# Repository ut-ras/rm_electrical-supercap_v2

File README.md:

# rm_electrical-supercap_v2

So i heard that having a readme is good and professional, so if anyone bothers to read this and is curious:
    The objective of the project is to use the excess allowed power draw. We chose the 90W at the time of writing I believe.
    Started out with a half bridge topology for the buck boose to/from 24V:3V supercaps.
    Apparently many compromises were made because Jed (Ged?) didn't want to use a microcontroller.
    So now we're at full bridge, using mspm0, with a lot of sensors and stuff so that zero voltage switching can be implemented to avoid power loss spike
    This specific branch, is a redesign to minimize powerpath (mainly), since we have more depth looking into the robot in our little compartment of space.

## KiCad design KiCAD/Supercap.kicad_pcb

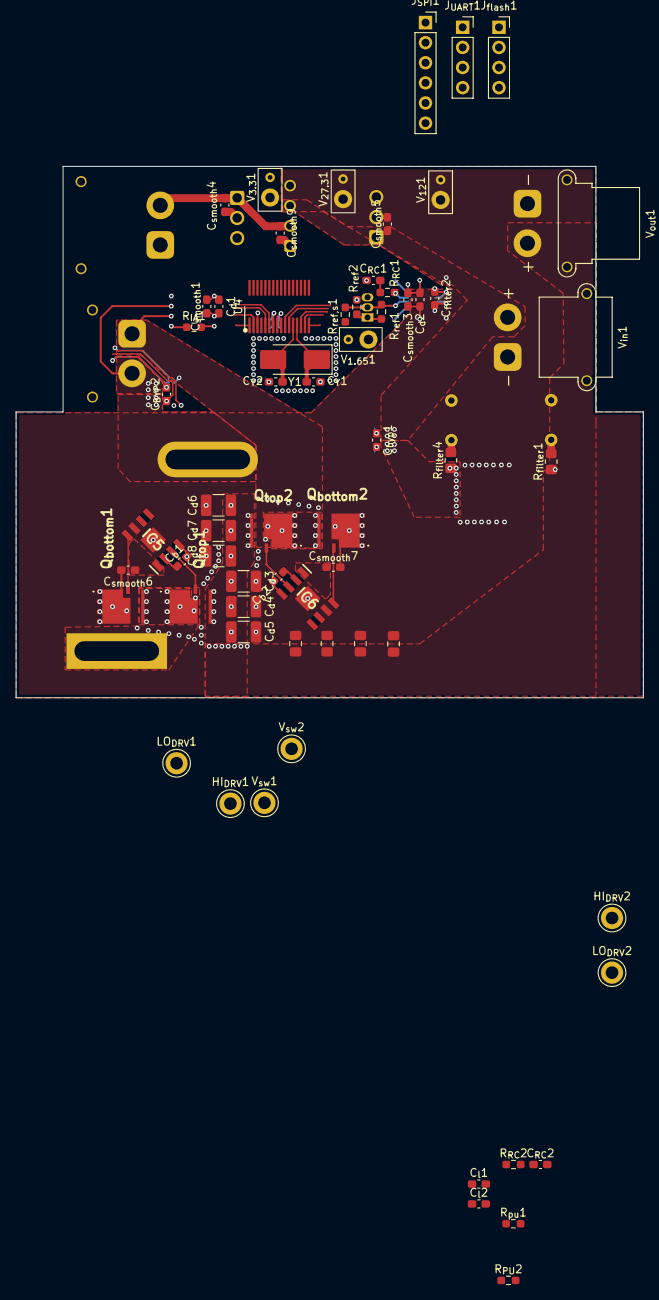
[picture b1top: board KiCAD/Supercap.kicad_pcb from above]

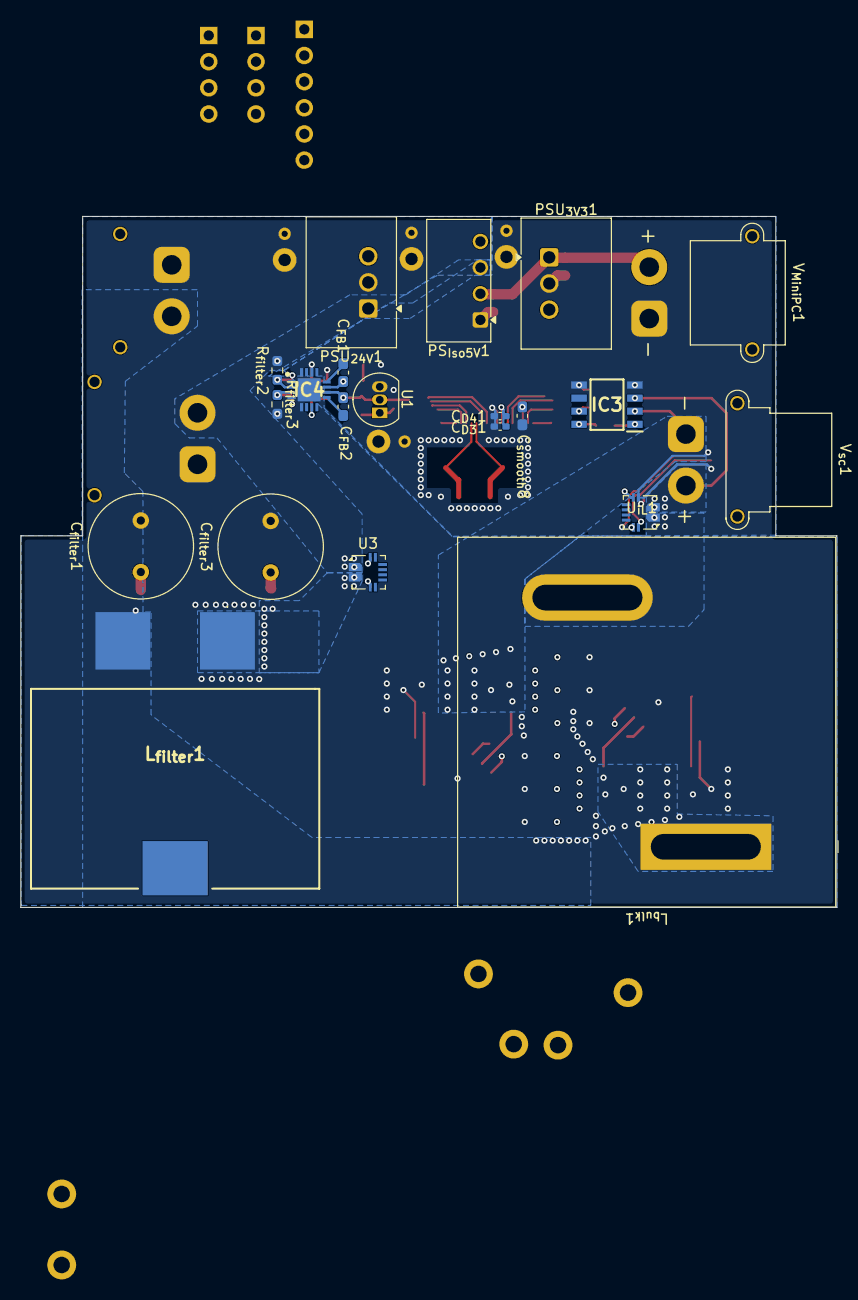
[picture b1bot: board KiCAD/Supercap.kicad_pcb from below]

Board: 4 copper layers, 79.2 x 67.1 mm, 84 parts (21 on the bottom side), 42 nets.

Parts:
C_{BYP}2: 0.1u; C_0603_1608Metric_Pad1.08x0.95mm_HandSolder
C_{D3}1: 100n; C_0402_1005Metric_Pad0.74x0.62mm_HandSolder
C_{D4}1: 10u; C_0402_1005Metric_Pad0.74x0.62mm_HandSolder
C_{FB}1, C_{FB}2: 100p; C_0603_1608Metric_Pad1.08x0.95mm_HandSolder
C_{RC}1, C_{RC}2: 1n; C_0603_1608Metric_Pad1.08x0.95mm_HandSolder
C_{Y}1, C_{Y}2: 10p; C_0603_1608Metric_Pad1.08x0.95mm_HandSolder
C_{bulk,out}1, C_{bulk,out}2, C_{bulk,out}3, C_{bulk,out}4: C_0805_2012Metric_Pad1.18x1.45mm_HandSolder
C_{byp}1: 0.1u; C_0603_1608Metric_Pad1.08x0.95mm_HandSolder
C_{b}1, C_{b}2: 1u; C_0603_1608Metric_Pad1.08x0.95mm_HandSolder
C_{d}1, C_{d}2: 0.1u; C_0603_1608Metric_Pad1.08x0.95mm_HandSolder
C_{d}3, C_{d}4, C_{d}5, C_{d}6, C_{d}7, C_{d}8: 10u; C_1210_3225Metric_Pad1.33x2.70mm_HandSolder
C_{filter}1, C_{filter}3: 1.2m; C_Radial_D10.0mm_H16.0mm_P5.00mm
C_{filter}2: 100p; C_0603_1608Metric_Pad1.08x0.95mm_HandSolder
C_{l}1, C_{l}2: 1n; C_0603_1608Metric_Pad1.08x0.95mm_HandSolder
C_{smooth}1, C_{smooth}3, C_{smooth}4, C_{smooth}5, C_{smooth}6, C_{smooth}7, C_{smooth}9: 4.7u; C_0603_1608Metric_Pad1.08x0.95mm_HandSolder
C_{smooth}8: 0.47u; C_0603_1608Metric_Pad1.08x0.95mm_HandSolder
HI_{DRV}1, HI_{DRV}2: TestPoint; TestPoint_Keystone_5010-5014_Multipurpose
IC3: INA823DT; SOIC127P600X175-8N
IC4: PGA849RGTR; QFN50P350X350X100-17N-D
IC5, IC6: MAX15019AASA+; SOIC127P600X175-9N
J_{SPI}1: Conn_01x06_Pin; PinSocket_1x06_P2.54mm_Vertical
J_{UART}1: Conn_01x04_Pin; PinSocket_1x04_P2.54mm_Vertical
J_{flash}1: Conn_01x04_Pin; PinSocket_1x04_P2.54mm_Vertical
LO_{DRV}1, LO_{DRV}2: TestPoint; TestPoint_Keystone_5010-5014_Multipurpose
L_{bulk}1: 27u; L_Wurth_WE-HCFT-3635_74437636352702
L_{filter}1: 33u; 74436413300
PSU_{3V3}1: TSR 0.5-2433; Converter_DCDC_TRACO_TSR0.5-24xx_TSR0.5-24xxx_THT
PSU_{24V}1: 490-P7812B-1000; Converter_DCDC_TRACO_TSR0.5-24xx_TSR0.5-24xxx_THT
PS_{Iso5V}1: SCT01F24S05; Converter_DCDC_TRACO_TEA1-xxxx_THT
Q_{bottom}1, Q_{bottom}2: IQDH45N04LM6CGSCATMA1
Q_{top}1, Q_{top}2: IQDH45N04LM6CGSCATMA1
R_{IA}1: 1M; R_0603_1608Metric_Pad0.98x0.95mm_HandSolder
R_{PU}2: 1k; R_0603_1608Metric_Pad0.98x0.95mm_HandSolder
R_{RC}1, R_{RC}2: 100; R_0603_1608Metric_Pad0.98x0.95mm_HandSolder
R_{filter}1, R_{filter}4: 0.5; R_0805_2012Metric_Pad1.20x1.40mm_HandSolder
R_{filter}2, R_{filter}3: 100; R_0603_1608Metric_Pad0.98x0.95mm_HandSolder
R_{pu}1: 100; R_0603_1608Metric_Pad0.98x0.95mm_HandSolder
R_{ref,s}1: 5.6k; R_0603_1608Metric_Pad0.98x0.95mm_HandSolder
R_{ref}1: 47k; R_0603_1608Metric_Pad0.98x0.95mm_HandSolder
R_{ref}2: 16k; R_0603_1608Metric_Pad0.98x0.95mm_HandSolder
U1: LM4041LP-ADJ; TO-92_Inline
U3: ACS71240KEXBLT-010B3; Allegro_QFN-12-10-1EP_3x3mm_P0.5mm
U4: M0G3507QDGS32RQ1; VSSOP_0.5mm_32pin_handsolder
U_{iL}1: ACS711xEXLT-31AB; Allegro_QFN-12-10-1EP_3x3mm_P0.5mm
V_{1.65}1, V_{3.3}1, V_{12}1, V_{27.3}1: TestPoint; TP_Passive
V_{MiniPC}1: AMASS_XT30PW-M_1x02_P2.50mm_Horizontal
V_{in}1: AMASS_XT30PW-M_1x02_P2.50mm_Horizontal
V_{out}1: AMASS_XT30PW-F_1x02_P2.50mm_Horizontal
V_{sc}1: AMASS_XT30PW-F_1x02_P2.50mm_Horizontal
V_{sw}1, V_{sw}2: TestPoint; TestPoint_Keystone_5010-5014_Multipurpose
Y1: Crystal; Crystal_SMD_Abracon_ABM3-2Pin_5.0x3.2mm_HandSoldering

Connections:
+3V3: C_{BYP}2.1, C_{D3}1.1, C_{D4}1.1, C_{byp}1.1, C_{d}2.1, C_{smooth}3.1, IC4.7 (LVDD), J_{flash}1.4, PSU_{3V3}1.3 (Vout), R_{PU}2.2, R_{pu}1.2, R_{ref,s}1.1, U3.10 (VCC), U4.7 (VDD), U_{iL}1.10 (VCC), V_{3.3}1.1
/Control/DA_{IN+}: C_{FB}2.2, IC4.9 (DA_IN+)
/Control/DA_{IN-}: C_{FB}1.1, IC4.12 (DA_IN-)
/Control/F_L: R_{PU}2.1, U_{iL}1.4 (~FAULT)
/Control/F_bat: R_{pu}1.1, U3.4 (~FAULT)
/Control/HFXIN: C_{Y}2.1, U4.12 (PA5/HFXIN/FCC_IN), Y1.2
/Control/HFXOUT: C_{Y}1.1, U4.13 (PA6/HFCLK_IN/HFXOUT), Y1.1
/Control/I_L: C_{l}2.1, U_{iL}1.9 (VIOUT)
/Control/I_bat: C_{l}1.1, U3.9 (VIOUT)
/Control/I_{L,-}: L_{bulk}1.2, U_{iL}1.1 (IP+)
/Control/I_{bat,out+}: C_{bulk,out}1.1, C_{bulk,out}2.1, C_{bulk,out}3.1, C_{bulk,out}4.1, C_{d}3.1, C_{d}4.1, C_{d}5.1, C_{d}6.1, C_{d}7.1, C_{d}8.1, L_{filter}1.2, Q_{top}1.1 (D), Q_{top}2.1 (D), R_{filter}1.1, V_{out}1.2 (+)
/Control/I_{bat,sense}: L_{filter}1.1, R_{filter}4.1, U3.2 (IP-)
/Control/RC_{filter,L}: C_{filter}3.1, R_{filter}4.2
/Control/RC_{filter,R}: C_{filter}1.1, R_{filter}1.2
/Control/R_{G1}: IC3.1 (RG_1), R_{IA}1.1
/Control/R_{G2}: IC3.8 (RG_2), R_{IA}1.2
/Control/SWCLK: J_{flash}1.2, U4.27 (PA20/SWCLK)
/Control/SWDIO: J_{flash}1.1, U4.26 (PA19/SWDIO)
/Control/V_{bat,sense}+: C_{filter}2.1, IC4.2 (IN+), R_{filter}2.1
/Control/V_{bat,sense}-: C_{filter}2.2, IC4.3 (IN-), R_{filter}3.1
/Control/V_{bat,sens}: C_{FB}1.2, IC4.11 (OUT), R_{RC}1.1
/Control/V_{core}: C_{smooth}8.1, U4.3 (VCORE)
/Control/V_{sc,+}: IC3.3 (+IN), U_{iL}1.2 (IP-), V_{sc}1.2 (+)
/Control/V_{sc,sens}: IC3.6 (OUT), R_{RC}2.1
/Housekeeping/+1V65: C_{FB}2.1, IC4.10 (REF), R_{ref,s}1.2, R_{ref}1.1, U1.2 (K), V_{1.65}1.1
/Housekeeping/+12V: C_{smooth}6.1, C_{smooth}7.1, IC5.1 (VDD), IC6.1 (VDD), PSU_{24V}1.3 (Vout), V_{12}1.1
/Housekeeping/+24V: C_{smooth}5.1, PSU_{24V}1.1 (Vin), PS_{Iso5V}1.3 (-VOUT), R_{filter}2.2, U3.1 (IP+), V_{in}1.2 (+)
/Housekeeping/+29V: C_{d}1.1, C_{smooth}1.1, IC3.7 (+VS), IC4.6 (VS+), PS_{Iso5V}1.4 (+VOUT), V_{27.3}1.1
/Housekeeping/MiniPC: C_{smooth}4.1, C_{smooth}9.1, PSU_{3V3}1.1 (Vin), PS_{Iso5V}1.2 (+VIN), V_{MiniPC}1.2 (+)
/Housekeeping/V_{fb,d}: R_{ref}1.2, R_{ref}2.1, U1.1 (FB)
/Voltage Converter/HI_DRV_{1}: HI_{DRV}1.1 (1_1), IC5.3 (OUT_H), Q_{top}1.2 (G)
/Voltage Converter/HI_DRV_{2}: HI_{DRV}2.1 (1_1), IC6.3 (OUT_H), Q_{top}2.2 (G)
/Voltage Converter/LO_DRV_{1}: IC5.8 (OUT_L), LO_{DRV}1.1 (1_1), Q_{bottom}1.2 (G)
/Voltage Converter/LO_DRV_{2}: IC6.8 (OUT_L), LO_{DRV}2.1 (1_1), Q_{bottom}2.2 (G)
/Voltage Converter/V_{boot}1: C_{b}1.1, IC5.2 (BST)
/Voltage Converter/V_{boot}2: C_{b}2.1, IC6.2 (BST)
/Voltage Converter/V_{sw,1}: C_{b}1.2, IC5.4 (SW), L_{bulk}1.1, Q_{bottom}1.1 (D), Q_{top}1.3 (S), V_{sw}1.1 (1_1)
/Voltage Converter/V_{sw,2}: C_{b}2.2, IC3.2 (-IN), IC6.4 (SW), Q_{bottom}2.1 (D), Q_{top}2.3 (S), V_{sc}1.1 (-), V_{sw}2.1 (1_1)
GND: C_{BYP}2.2, C_{D3}1.2, C_{D4}1.2, C_{RC}1.2, C_{RC}2.2, C_{Y}1.2, C_{Y}2.2, C_{byp}1.2, C_{d}1.2, C_{d}2.2, C_{l}1.2, C_{l}2.2, C_{smooth}1.2, C_{smooth}3.2, C_{smooth}4.2, C_{smooth}8.2, C_{smooth}9.2, IC3.4 (-VS), IC3.5 (REF), IC4.14 (LVSS), IC4.16 (DGND), J_{flash}1.3, PSU_{3V3}1.2 (GND), PS_{Iso5V}1.1 (-VIN), R_{ref}2.2, U1.3 (A), U3.3 (GND), U4.8 (VSS), U_{iL}1.3 (GND), V_{1.65}1.2, V_{3.3}1.2, V_{MiniPC}1.1 (-)
GNDPWR: C_{bulk,out}1.2, C_{bulk,out}2.2, C_{bulk,out}3.2, C_{bulk,out}4.2, C_{d}3.2, C_{d}4.2, C_{d}5.2, C_{d}6.2, C_{d}7.2, C_{d}8.2, C_{filter}1.2, C_{filter}3.2, C_{smooth}5.2, C_{smooth}6.2, C_{smooth}7.2, IC4.1 (A2), IC4.4 (A0), IC4.5 (A1), IC4.15 (VS-), IC4.17 (VS-), IC5.7 (GND), IC5.9 (GND), IC6.7 (GND), IC6.9 (GND), PSU_{24V}1.2 (GND), Q_{bottom}1.3 (S), Q_{bottom}2.3 (S), R_{filter}3.2, V_{12}1.2, V_{27.3}1.2, V_{in}1.1 (-), V_{out}1.1 (-)
unnamed: C_{RC}1.1, R_{RC}1.2
unnamed: C_{RC}2.1, R_{RC}2.2

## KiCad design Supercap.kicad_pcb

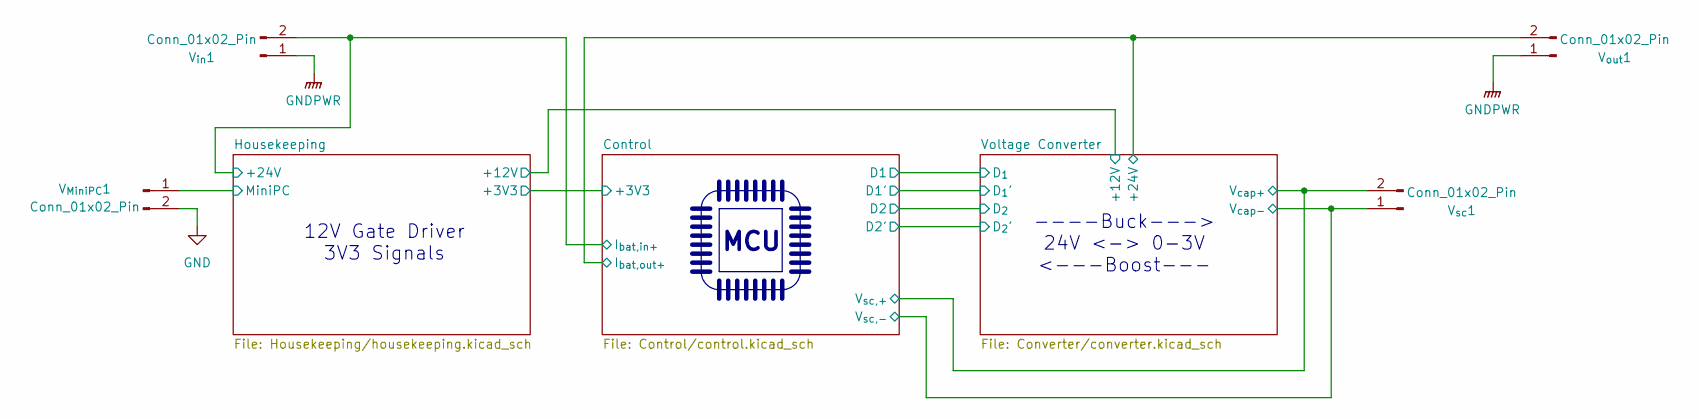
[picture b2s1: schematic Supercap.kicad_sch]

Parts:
V_{MiniPC}1: Conn_01x02_Pin; AMASS_XT30PW-F_1x02_P2.50mm_Horizontal
V_{in}1: Conn_01x02_Pin; AMASS_XT30PW-M_1x02_P2.50mm_Horizontal
V_{out}1: Conn_01x02_Pin; AMASS_XT30PW-F_1x02_P2.50mm_Horizontal
V_{sc}1: Conn_01x02_Pin; AMASS_XT30PW-M_1x02_P2.50mm_Horizontal

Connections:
/Control/I_{bat,in+}: V_{in}1.2; also elsewhere on the board
/Control/I_{bat,out+}: V_{out}1.2; also elsewhere on the board
/Control/V_{sc,+}: V_{sc}1.2; also elsewhere on the board
/Housekeeping/MiniPC: V_{MiniPC}1.1; also elsewhere on the board
/Voltage Converter/V_{sw,2}: V_{sc}1.1; also elsewhere on the board
GND: V_{MiniPC}1.2; also elsewhere on the board
GNDPWR: V_{in}1.1, V_{out}1.1; also elsewhere on the board

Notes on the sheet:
----Buck---> 24V <-> 0-3V <---Boost---
MCU
12V Gate Driver 3V3 Signals

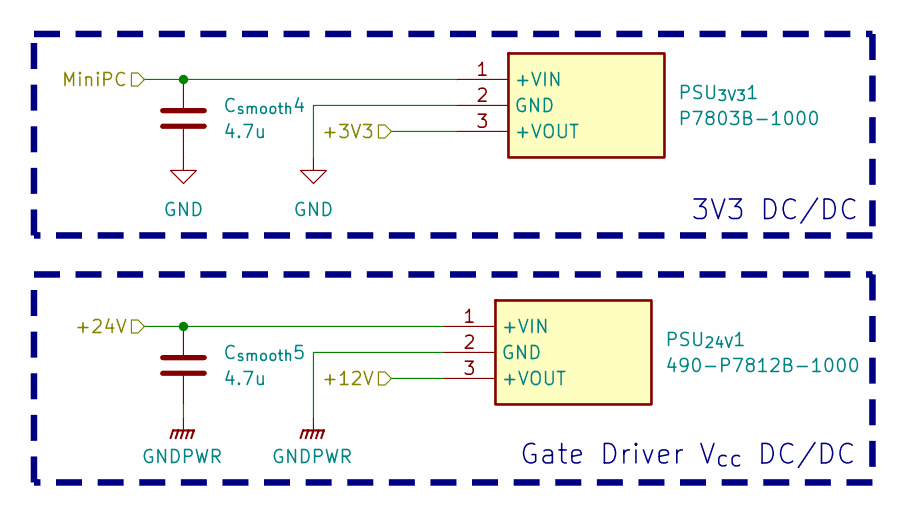
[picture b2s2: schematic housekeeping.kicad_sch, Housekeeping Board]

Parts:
C_{smooth}4, C_{smooth}5: 4.7u; C_0603_1608Metric_Pad1.08x0.95mm_HandSolder; Manufacturer_Part_Number CL10A475KO8NNNC; Mouser Part Number 187-CL10A475KO8NNNC
PSU_{3V3}1: P7803B-1000; P7812B1000; Manufacturer_Part_Number P7803B-1000; Mouser Part Number 490-P7803B-1000
PSU_{24V}1: 490-P7812B-1000; P7812B1000; Manufacturer_Part_Number P7812B-1000; Mouser Part Number 490-P7812B-1000

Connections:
/Control/+3V3: PSU_{3V3}1.3 (+VOUT); also elsewhere on the board
/Control/I_{bat,in+}: C_{smooth}5.1, PSU_{24V}1.1 (+VIN); also elsewhere on the board
/Housekeeping/+12V: PSU_{24V}1.3 (+VOUT); also elsewhere on the board
/Housekeeping/MiniPC: C_{smooth}4.1, PSU_{3V3}1.1 (+VIN); also elsewhere on the board
GND: C_{smooth}4.2, PSU_{3V3}1.2 (GND); also elsewhere on the board
GNDPWR: C_{smooth}5.2, PSU_{24V}1.2 (GND); also elsewhere on the board

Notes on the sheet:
Gate Driver V_{cc} DC/DC
3V3 DC/DC

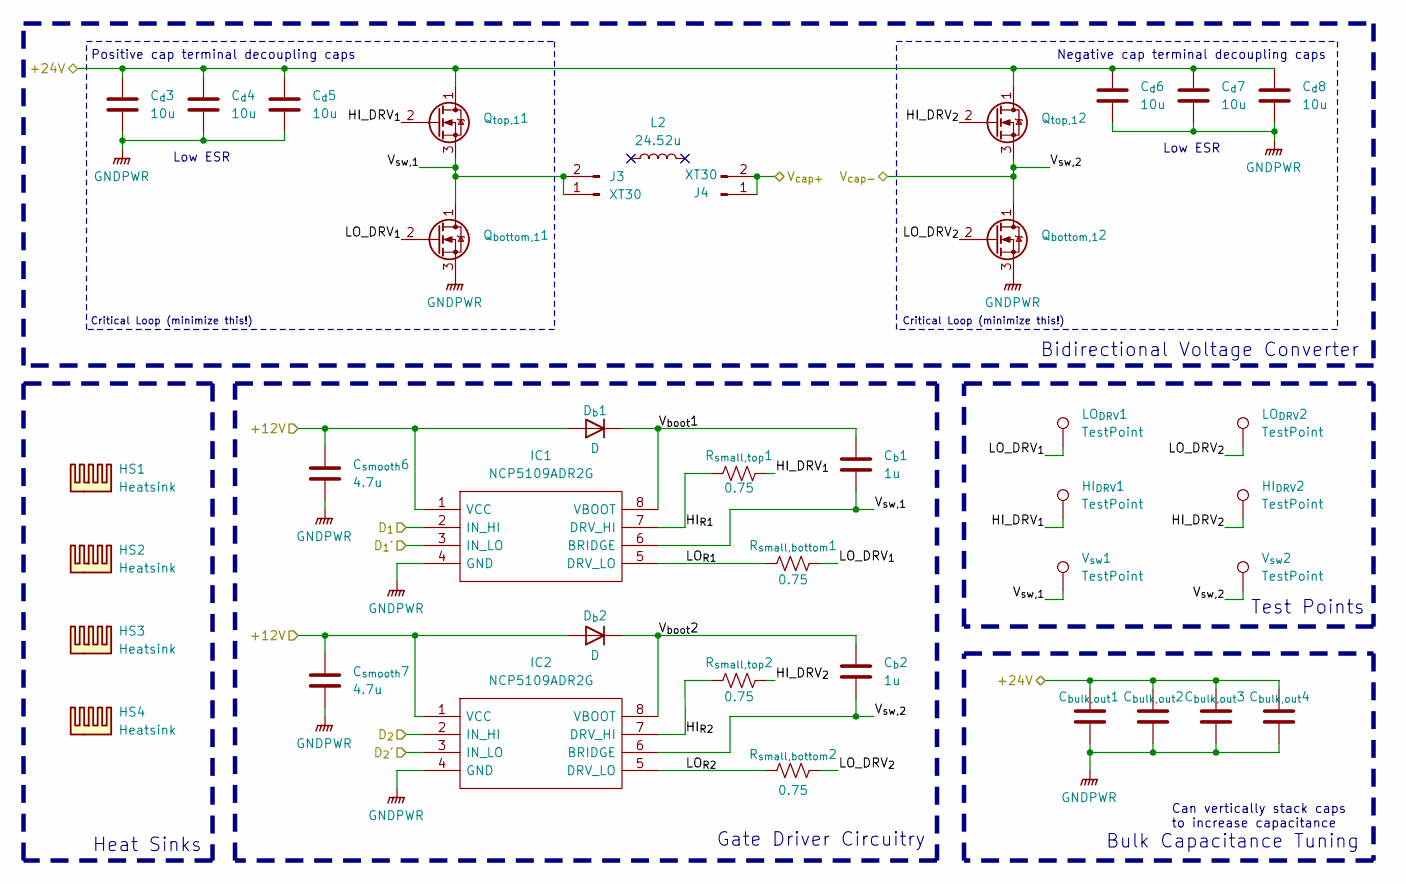
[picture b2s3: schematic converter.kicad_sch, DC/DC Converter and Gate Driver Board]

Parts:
C_{bulk,out}1, C_{bulk,out}2, C_{bulk,out}3, C_{bulk,out}4: C_0603_1608Metric_Pad1.08x0.95mm_HandSolder; Voltage Rating 50V
C_{b}1, C_{b}2: 1u; C_0603_1608Metric_Pad1.08x0.95mm_HandSolder; Manufacturer_Part_Number 963-MAJCT168BB7105KT; Mouser Part Number 963-MAJCT168BB7105KT
C_{d}3, C_{d}4, C_{d}5, C_{d}6, C_{d}7, C_{d}8: 10u; C_1210_3225Metric_Pad1.33x2.70mm_HandSolder; Voltage Rating 50V; Mouser Part Number 187-CL32B106KMVNNWE
C_{smooth}6, C_{smooth}7: 4.7u; C_0603_1608Metric_Pad1.08x0.95mm_HandSolder; Manufacturer_Part_Number CL10A475KO8NNNC; Mouser Part Number 187-CL10A475KO8NNNC
D_{b}1, D_{b}2: D; D_MicroSMP_AK; Manufacturer_Part_Number V1P22HM3_A/H; Mouser Part Number 78-V1P22HM3_A/H
HI_{DRV}1, HI_{DRV}2: TestPoint; TestPoint_Bridge_Pitch2.0mm_Drill0.7mm
HS1, HS2, HS3, HS4: Heatsink; Manufacturer_Part_Number HSB01-080808; Mouser Part Number 490-HSB01-080808
IC1, IC2: NCP5109ADR2G; SOIC127P600X175-8N; Mouser Part Number 863-NCP5109ADR2G
J3, J4: XT30; AMASS_XT30UPB-F_1x02_P5.0mm_Vertical
L2: 24.52u
LO_{DRV}1, LO_{DRV}2: TestPoint; TestPoint_Bridge_Pitch2.0mm_Drill0.7mm
Q_{bottom,1}1, Q_{bottom,1}2: IQDH45N04LM6CGSCATMA1; Manufacturer_Part_Number IQDH35N03LM5CGSCATMA1; Mouser Part Number 726-IQDH35N03LM5CGSC
Q_{top,1}1, Q_{top,1}2: IQDH45N04LM6CGSCATMA1; Manufacturer_Part_Number IQDH35N03LM5CGSCATMA1; Mouser Part Number 726-IQDH35N03LM5CGSC
R_{small,bottom}1, R_{small,bottom}2: 0.75; R_0603_1608Metric_Pad0.98x0.95mm_HandSolder; Manufacturer_Part_Number RL0603FR-070R75L; Mouser Part Number 603-RL0603FR-070R75L
R_{small,top}1, R_{small,top}2: 0.75; R_0603_1608Metric_Pad0.98x0.95mm_HandSolder; Manufacturer_Part_Number RL0603FR-070R75L; Mouser Part Number 603-RL0603FR-070R75L
V_{sw}1, V_{sw}2: TestPoint; TestPoint_Bridge_Pitch2.0mm_Drill0.7mm

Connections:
/Control/I_{bat,out+}: C_{bulk,out}1.1, C_{bulk,out}2.1, C_{bulk,out}3.1, C_{bulk,out}4.1, C_{d}3.1, C_{d}4.1, C_{d}5.1, C_{d}6.1, C_{d}7.1, C_{d}8.1, Q_{top,1}1.1 (D), Q_{top,1}2.1 (D); also elsewhere on the board
/Control/PA8: IC1.2 (IN_HI); also elsewhere on the board
/Control/PA22: IC1.3 (IN_LO); also elsewhere on the board
/Control/PA25: IC2.3 (IN_LO); also elsewhere on the board
/Control/PB9: IC2.2 (IN_HI); also elsewhere on the board
/Control/V_{sc,+}: J4.1, J4.2; also elsewhere on the board
/Housekeeping/+12V: C_{smooth}6.1, C_{smooth}7.1, D_{b}1.2 (A), D_{b}2.2 (A), IC1.1 (VCC), IC2.1 (VCC); also elsewhere on the board
/Voltage Converter/HI_DRV_{1}: HI_{DRV}1.1, Q_{top,1}1.2 (G), R_{small,top}1.2
/Voltage Converter/HI_DRV_{2}: HI_{DRV}2.1, Q_{top,1}2.2 (G), R_{small,top}2.2
/Voltage Converter/HI_{R1}: IC1.7 (DRV_HI), R_{small,top}1.1
/Voltage Converter/HI_{R2}: IC2.7 (DRV_HI), R_{small,top}2.1
/Voltage Converter/LO_DRV_{1}: LO_{DRV}1.1, Q_{bottom,1}1.2 (G), R_{small,bottom}1.2
/Voltage Converter/LO_DRV_{2}: LO_{DRV}2.1, Q_{bottom,1}2.2 (G), R_{small,bottom}2.2
/Voltage Converter/LO_{R1}: IC1.5 (DRV_LO), R_{small,bottom}1.1
/Voltage Converter/LO_{R2}: IC2.5 (DRV_LO), R_{small,bottom}2.1
/Voltage Converter/V_{boot}1: C_{b}1.1, D_{b}1.1 (K), IC1.8 (VBOOT)
/Voltage Converter/V_{boot}2: C_{b}2.1, D_{b}2.1 (K), IC2.8 (VBOOT)
/Voltage Converter/V_{sw,1}: C_{b}1.2, IC1.6 (BRIDGE), J3.1, J3.2, Q_{bottom,1}1.1 (D), Q_{top,1}1.3 (S), V_{sw}1.1
/Voltage Converter/V_{sw,2}: C_{b}2.2, IC2.6 (BRIDGE), Q_{bottom,1}2.1 (D), Q_{top,1}2.3 (S), V_{sw}2.1; also elsewhere on the board
GNDPWR: C_{bulk,out}1.2, C_{bulk,out}2.2, C_{bulk,out}3.2, C_{bulk,out}4.2, C_{d}3.2, C_{d}4.2, C_{d}5.2, C_{d}6.2, C_{d}7.2, C_{d}8.2, C_{smooth}6.2, C_{smooth}7.2, IC1.4 (GND), IC2.4 (GND), Q_{bottom,1}1.3 (S), Q_{bottom,1}2.3 (S); also elsewhere on the board

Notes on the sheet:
Heat Sinks
Critical Loop (minimize this!)
Negative cap terminal decoupling caps
Test Points
Bidirectional Voltage Converter
Bulk Capacitance Tuning
Gate Driver Circuitry
Low ESR
Can vertically stack caps to increase capacitance
Positive cap terminal decoupling caps

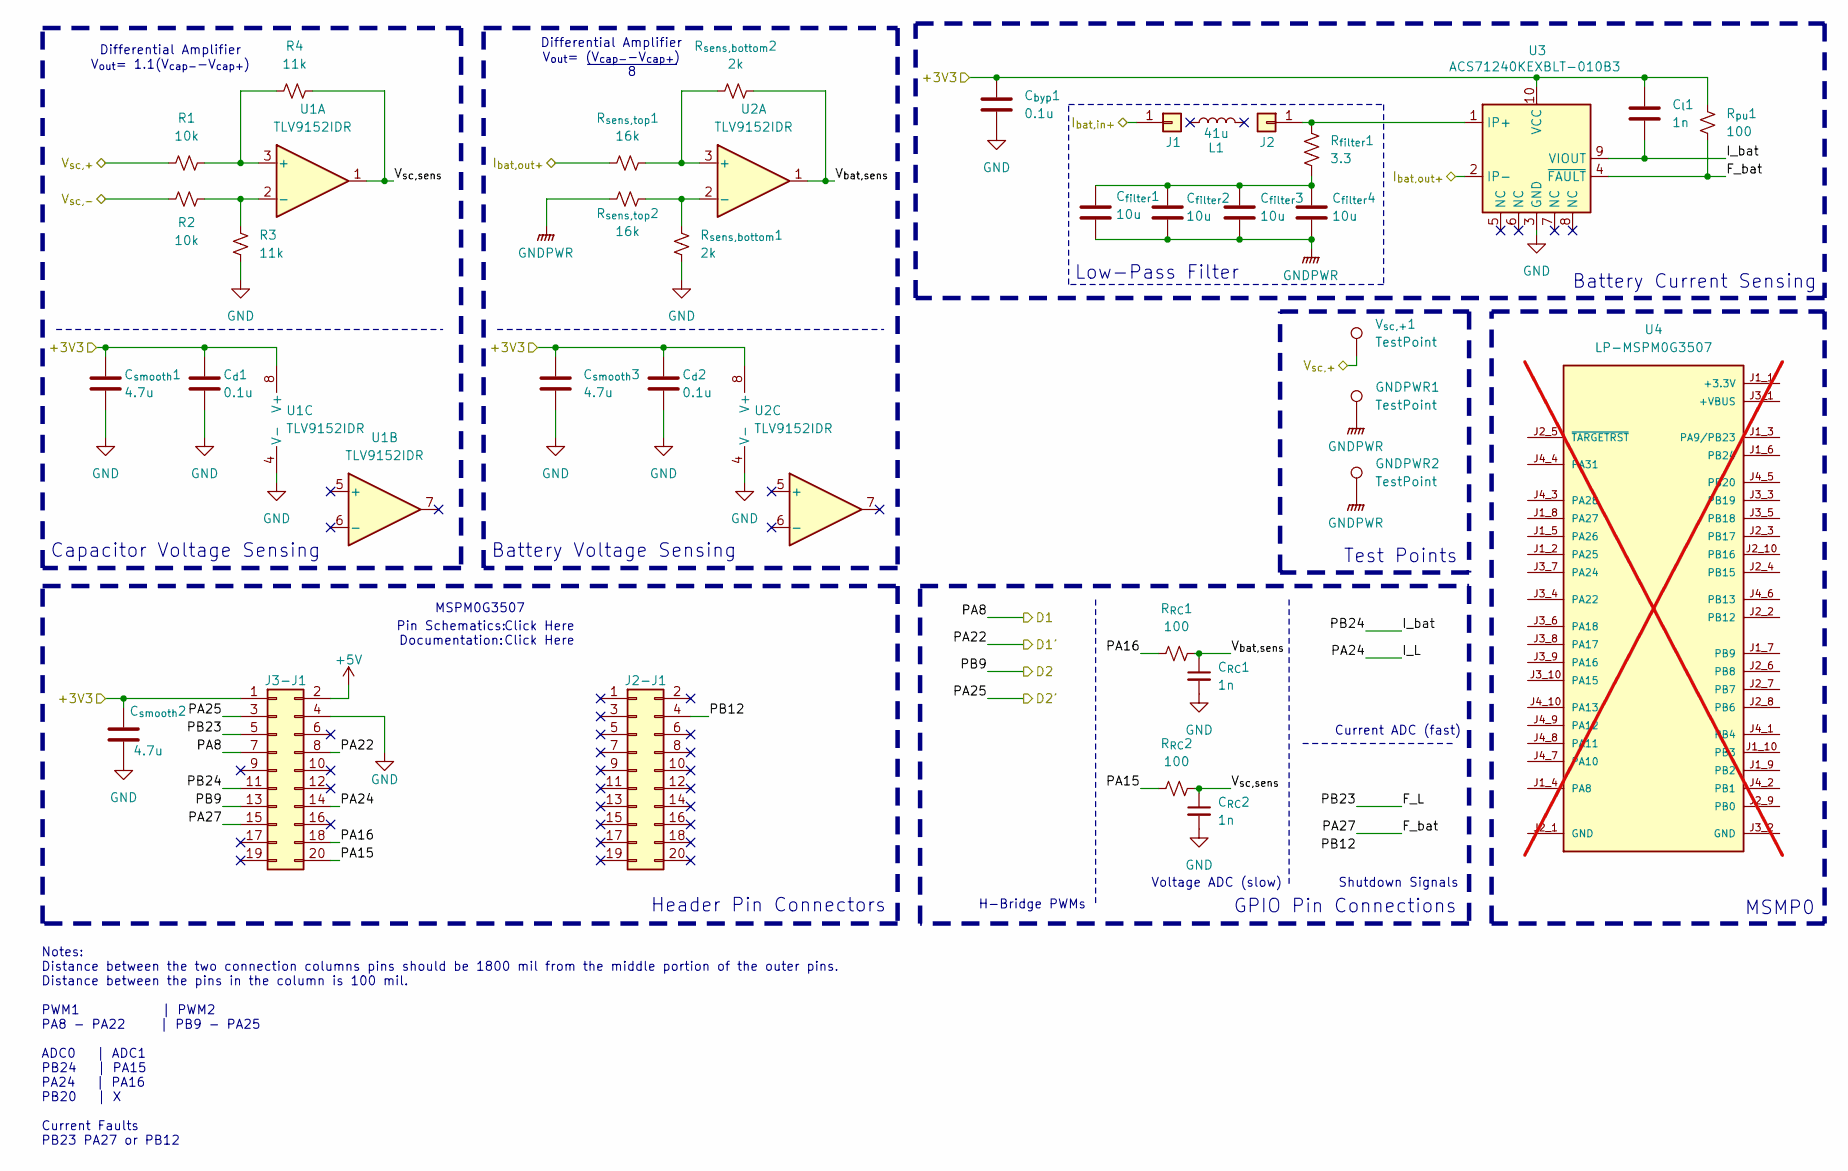
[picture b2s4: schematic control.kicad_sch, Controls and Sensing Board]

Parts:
C_{RC}1, C_{RC}2: 1n; C_0603_1608Metric_Pad1.08x0.95mm_HandSolder; Manufacturer_Part_Number CC0603JRX7R7BB102; Mouser Part Number 603-CC0603JR7R7BB102
C_{byp}1: 0.1u; C_0603_1608Metric_Pad1.08x0.95mm_HandSolder; Manufacturer_Part_Number MCAST168SB5104KTNA01; Mouser Part Number 963-MCAST168SB5104KT
C_{d}1, C_{d}2: 0.1u; C_0603_1608Metric_Pad1.08x0.95mm_HandSolder; Manufacturer_Part_Number KGM15BR71H104JM; Mouser Part Number 581-KGM15BR71H104JM
C_{filter}1, C_{filter}2, C_{filter}3, C_{filter}4: 10u; C_0603_1608Metric_Pad1.08x0.95mm_HandSolder; Mouser# 81-GRM188R6YA106MA3D
C_{l}1: 1n; C_0603_1608Metric_Pad1.08x0.95mm_HandSolder; Manufacturer_Part_Number CC0603JRX7R7BB102; Mouser Part Number 603-CC0603JR7R7BB102
C_{smooth}1, C_{smooth}2, C_{smooth}3: 4.7u; C_0603_1608Metric_Pad1.08x0.95mm_HandSolder; Manufacturer_Part_Number CL10A475KO8NNNC; Mouser Part Number 187-CL10A475KO8NNNC
GNDPWR1, GNDPWR2: TestPoint; TestPoint_Bridge_Pitch2.0mm_Drill0.7mm
J1, J2: Conn_01x01; Inductor_wire_conn
J2-J1, J3-J1: Conn_01x10; PinSocket_2x10_P2.54mm_Vertical; Manufacturer_Part_Number 2044-2X10G00SA; Digi-Key Part Number 2553-2044-2X10G00SA-ND
L1: 41u
R1, R2: 10k; R_0603_1608Metric_Pad0.98x0.95mm_HandSolder; Manufacturer_Part_Number RN73R1JTTD1002B50; Mouser Part Number 660-RN73R1JTD1002B50
R3, R4: 11k; R_0603_1608Metric_Pad0.98x0.95mm_HandSolder; Manufacturer_Part_Number RN73R1JTTD1102B25; Mouser Part Number 660-RN73R1JTD1102B25
R_{RC}1, R_{RC}2: 100; R_0603_1608Metric_Pad0.98x0.95mm_HandSolder; Manufacturer_Part_Number CRGCQ0603F100R; Mouser Part Number 279-CRGCQ0603F100R
R_{filter}1: 3.3; R_0603_1608Metric_Pad0.98x0.95mm_HandSolder; Manufacturer_Part_Number ERJ-H3QD3R30V; Mouser Part Number 667-ERJ-H3QD3R30V
R_{pu}1: 100; R_0603_1608Metric_Pad0.98x0.95mm_HandSolder; Manufacturer_Part_Number CRGCQ0603F100R; Mouser Part Number 279-CRGCQ0603F100R
R_{sens,bottom}1, R_{sens,bottom}2: 2k; R_0603_1608Metric_Pad0.98x0.95mm_HandSolder; Manufacturer_Part_Number AT0603DRD072KL; Mouser Part Number 603-AT0603DRD072KL
R_{sens,top}1, R_{sens,top}2: 16k; R_0603_1608Metric_Pad0.98x0.95mm_HandSolder; Manufacturer_Part_Number RT0603DRD0716KL; Mouser Part Number 603-RT0603DRD0716KL
U1, U2: TLV9152IDR; SOIC-8_3.9x4.9mm_P1.27mm; Manufacturer_Part_Number TLV9152IDR; Mouser Part Number 595-TLV9152IDR
U3: ACS71240KEXBLT-010B3; Allegro_QFN-12-10-1EP_3x3mm_P0.5mm; Manufacturer_Part_Number ACS71240KEXBLT-010B3; Mouser Part Number 250-71240KEXBLT010B3
U4: LP-MSPM0G3507; ti_LP_MSPM0G3507; not fitted
V_{sc,+}1: TestPoint; TestPoint_Bridge_Pitch2.0mm_Drill0.7mm

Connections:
+5V: J3-J1.2
/Control/+3V3: C_{byp}1.1, C_{d}1.1, C_{d}2.1, C_{l}1.1, C_{smooth}1.1, C_{smooth}2.1, C_{smooth}3.1, J3-J1.1, R_{pu}1.2, U1.8 (V+), U2.8 (V+), U3.10 (VCC); also elsewhere on the board
/Control/F_L: J3-J1.5
/Control/F_bat: J3-J1.15, R_{pu}1.1, U3.4 (~FAULT)
/Control/I_L: J3-J1.14
/Control/I_bat: C_{l}1.2, J3-J1.11, U3.9 (VIOUT)
/Control/I_{bat,in+}: J1.1; also elsewhere on the board
/Control/I_{bat,out+}: R_{sens,top}1.1, U3.2 (IP-); also elsewhere on the board
/Control/PA8: J3-J1.7; also elsewhere on the board
/Control/PA15: J3-J1.20, R_{RC}2.2
/Control/PA16: J3-J1.18, R_{RC}1.2
/Control/PA22: J3-J1.8; also elsewhere on the board
/Control/PA25: J3-J1.3; also elsewhere on the board
/Control/PB9: J3-J1.13; also elsewhere on the board
/Control/PB12: J2-J1.4
/Control/V_{bat,sens}: C_{RC}1.1, R_{RC}1.1, R_{sens,bottom}2.2, U2.1
/Control/V_{sc,+}: R1.1, V_{sc,+}1.1; also elsewhere on the board
/Control/V_{sc,sens}: C_{RC}2.1, R4.2, R_{RC}2.1, U1.1
/Voltage Converter/V_{sw,2}: R2.1; also elsewhere on the board
GND: C_{RC}1.2, C_{RC}2.2, C_{byp}1.2, C_{d}1.2, C_{d}2.2, C_{smooth}1.2, C_{smooth}2.2, C_{smooth}3.2, J3-J1.4, R3.2, R_{sens,bottom}1.1, U1.4 (V-), U2.4 (V-), U3.3 (GND); also elsewhere on the board
GNDPWR: C_{filter}1.2, C_{filter}2.2, C_{filter}3.2, C_{filter}4.2, GNDPWR1.1, GNDPWR2.1, R_{sens,top}2.1; also elsewhere on the board
unnamed: C_{filter}1.1, C_{filter}2.1, C_{filter}3.1, C_{filter}4.1, R_{filter}1.2
unnamed: J2.1, R_{filter}1.1, U3.1 (IP+)
unnamed: R1.2, R4.1, U1.3 (+)
unnamed: R2.2, R3.1, U1.2 (-)
unnamed: R_{sens,bottom}2.1, R_{sens,top}1.2, U2.3 (+)
unnamed: R_{sens,bottom}1.2, R_{sens,top}2.2, U2.2 (-)

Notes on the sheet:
Shutdown Signals
Pin Schematics: Documentation:
MSMP0
MSPM0G3507
Battery Current Sensing
Current ADC (fast)
Low-Pass Filter
Voltage ADC (slow)
Header Pin Connectors
Click Here
Differential Amplifier V_{out}= (V_{cap-}-V_{cap+}) ~{ 8 }
Test Points
GPIO Pin Connections
H-Bridge PWMs
Capacitor Voltage Sensing
Battery Voltage Sensing
Differential Amplifier V_{out}= 1.1(V_{cap-}-V_{cap+})
Notes: Distance between the two connection columns pins should be 1800 mil from the middle portion of the outer pins. Distance between the pins in the column is 100 mil. PWM1 | PWM2 PA8 - PA22 | PB9 - PA25 ADC0 | ADC1 PB24 | PA15 PA24 | PA16 PB20 | X Current Faults PB23 PA27 or PB12

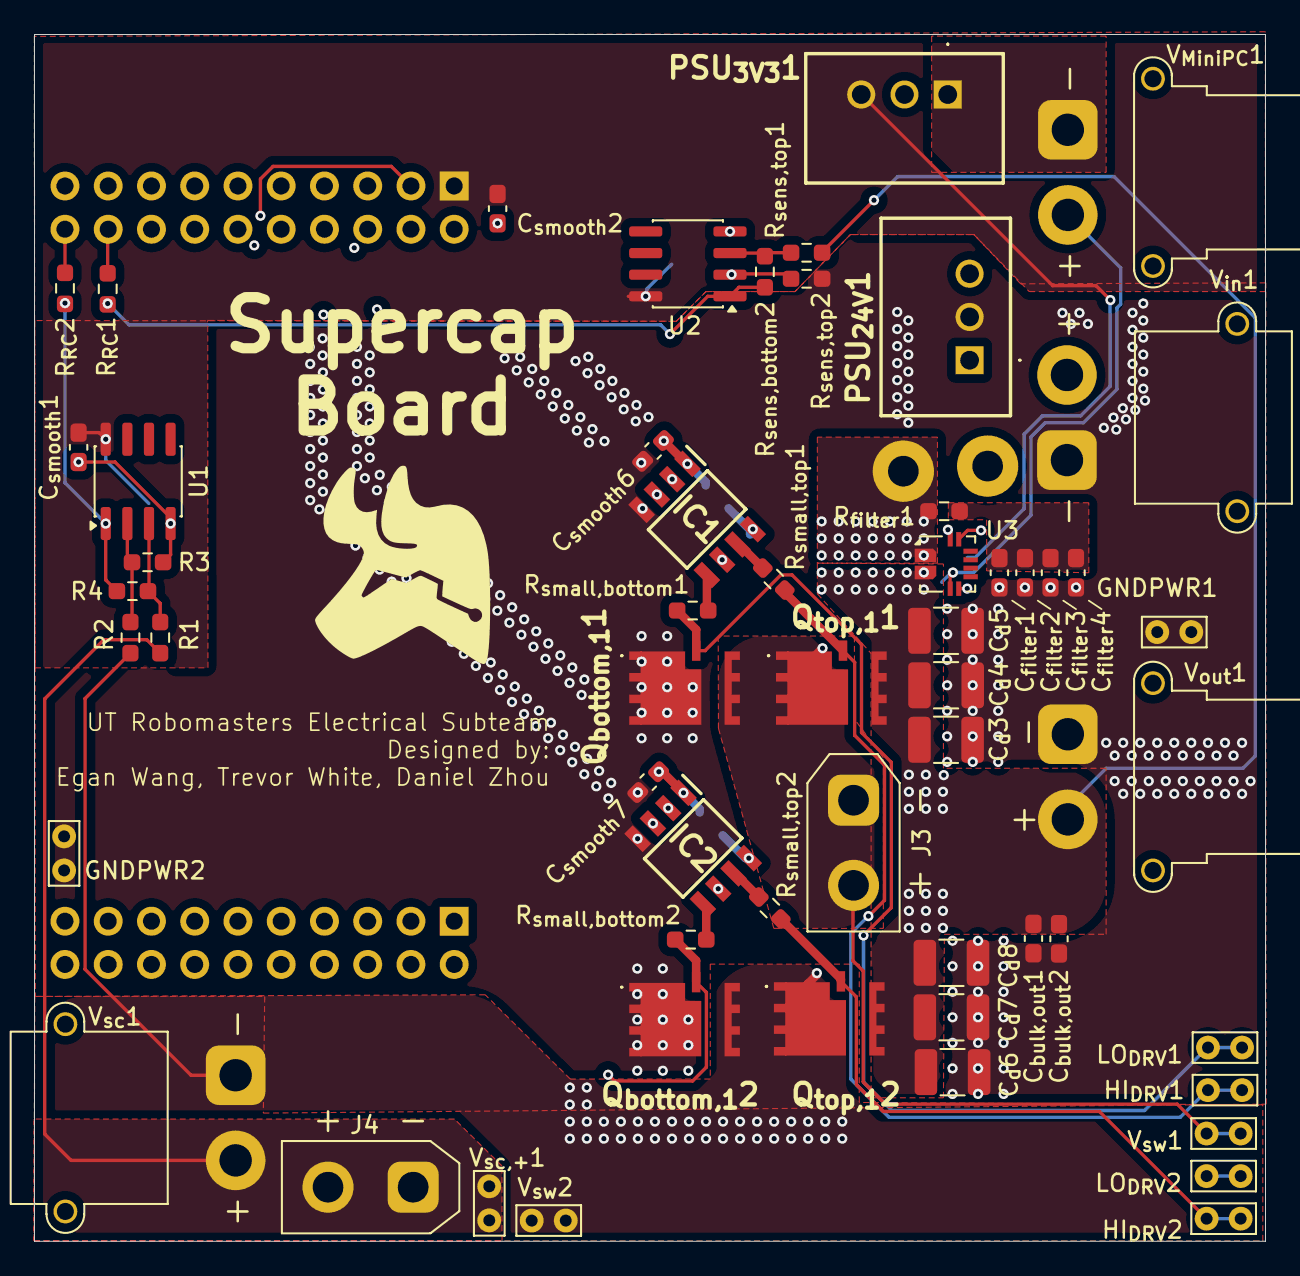
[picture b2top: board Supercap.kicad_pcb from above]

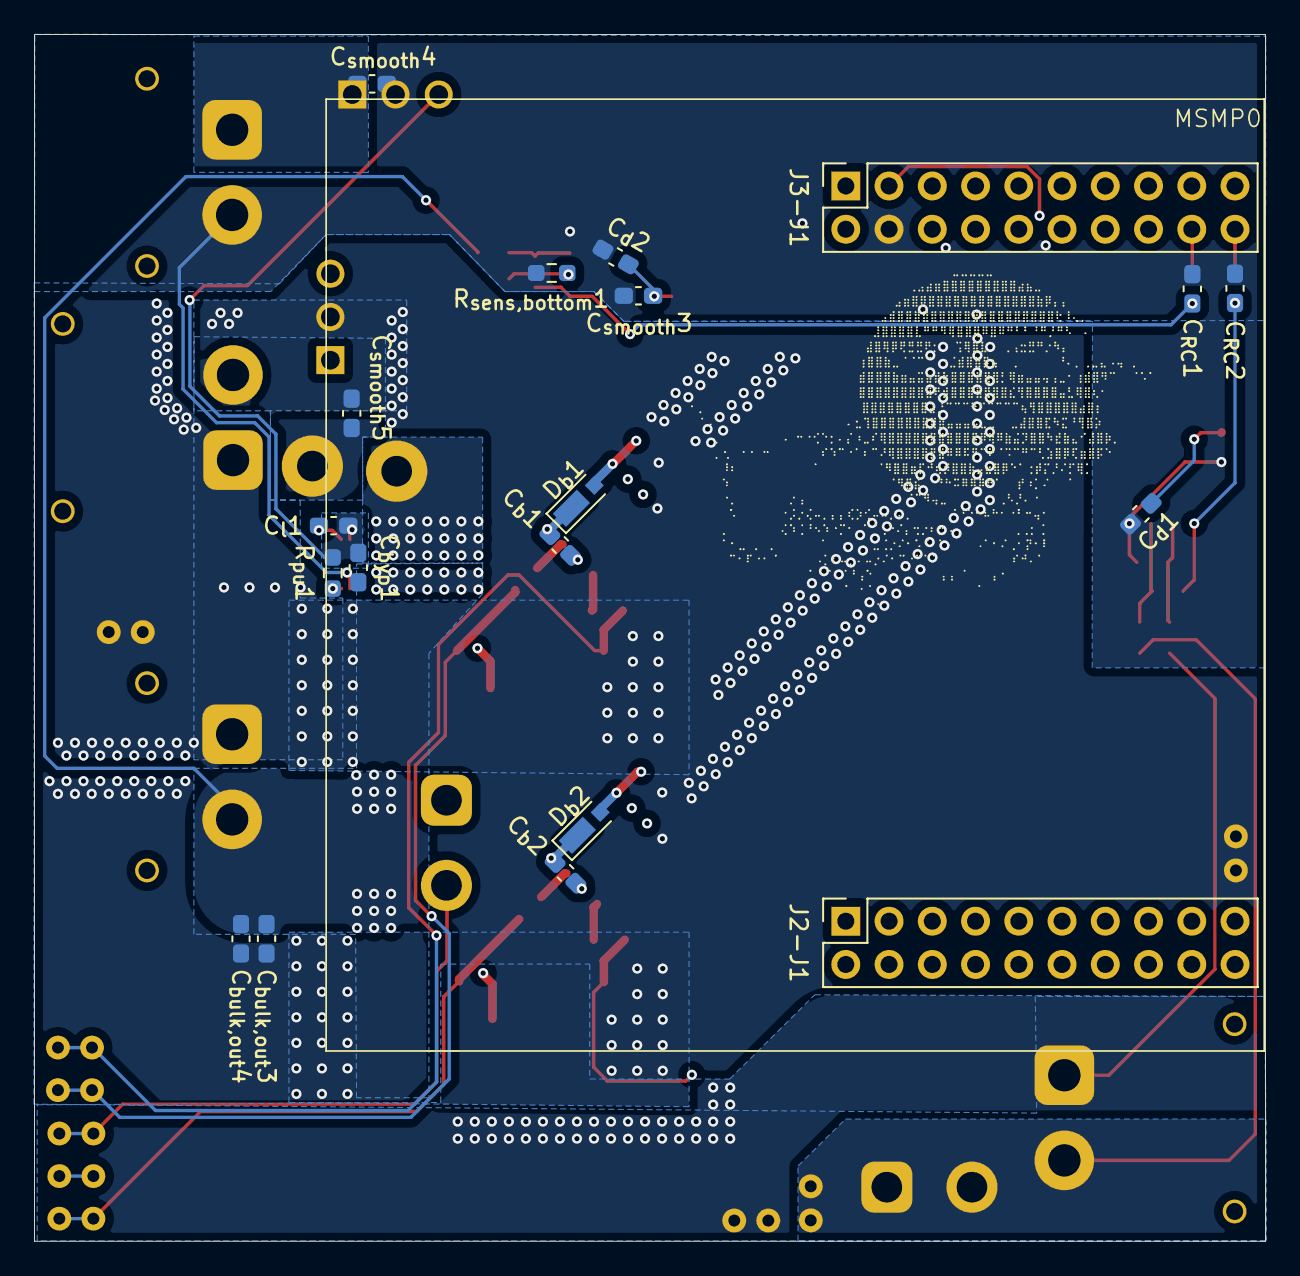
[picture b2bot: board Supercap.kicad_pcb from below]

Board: 4 copper layers, 72.3 x 70.9 mm, 77 parts (20 on the bottom side), 36 nets.

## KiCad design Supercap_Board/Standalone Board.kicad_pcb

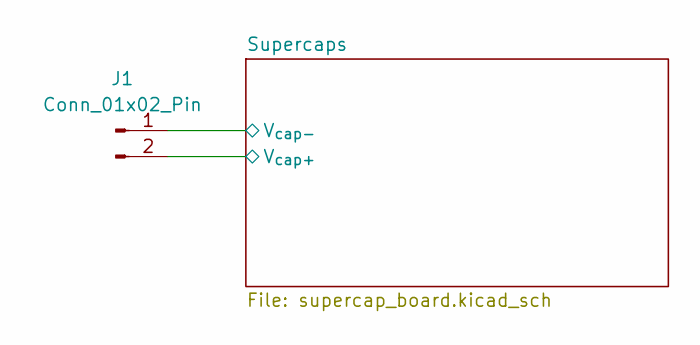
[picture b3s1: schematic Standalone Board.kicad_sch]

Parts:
J1: Conn_01x02_Pin; AMASS_XT30UPB-F_1x02_P5.0mm_Vertical

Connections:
/Supercaps/V_{cap+}: J1.2; also elsewhere on the board
/Supercaps/V_{cap-}: J1.1; also elsewhere on the board

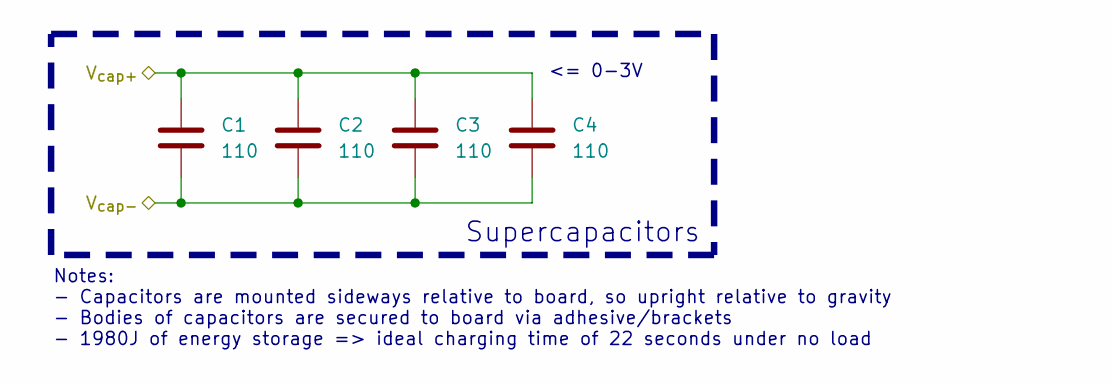
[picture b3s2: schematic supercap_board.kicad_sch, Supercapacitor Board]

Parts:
C1, C2, C3, C4: 110; C_Radial_D18.0mm_H35.5mm_P7.50mm; Voltage Rating 3V; Mouser Part Number 598-DSF117Q3R0

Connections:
/Supercaps/V_{cap+}: C1.1, C2.1, C3.1, C4.1; also elsewhere on the board
/Supercaps/V_{cap-}: C1.2, C2.2, C3.2, C4.2; also elsewhere on the board

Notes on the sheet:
Notes: - Capacitors are mounted sideways relative to board, so upright relative to gravity - Bodies of capacitors are secured to board via adhesive/brackets - 1980J of energy storage => ideal charging time of 22 seconds under no load
Supercapacitors
<= 0-3V

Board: 2 copper layers, 5 parts (0 on the bottom side), 2 nets, no tracks yet.
